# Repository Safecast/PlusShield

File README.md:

PlusShield
==========

The arduino shield for the bGeigie+. Version 1.0.
By Robin Scheibler and Joe Moross.

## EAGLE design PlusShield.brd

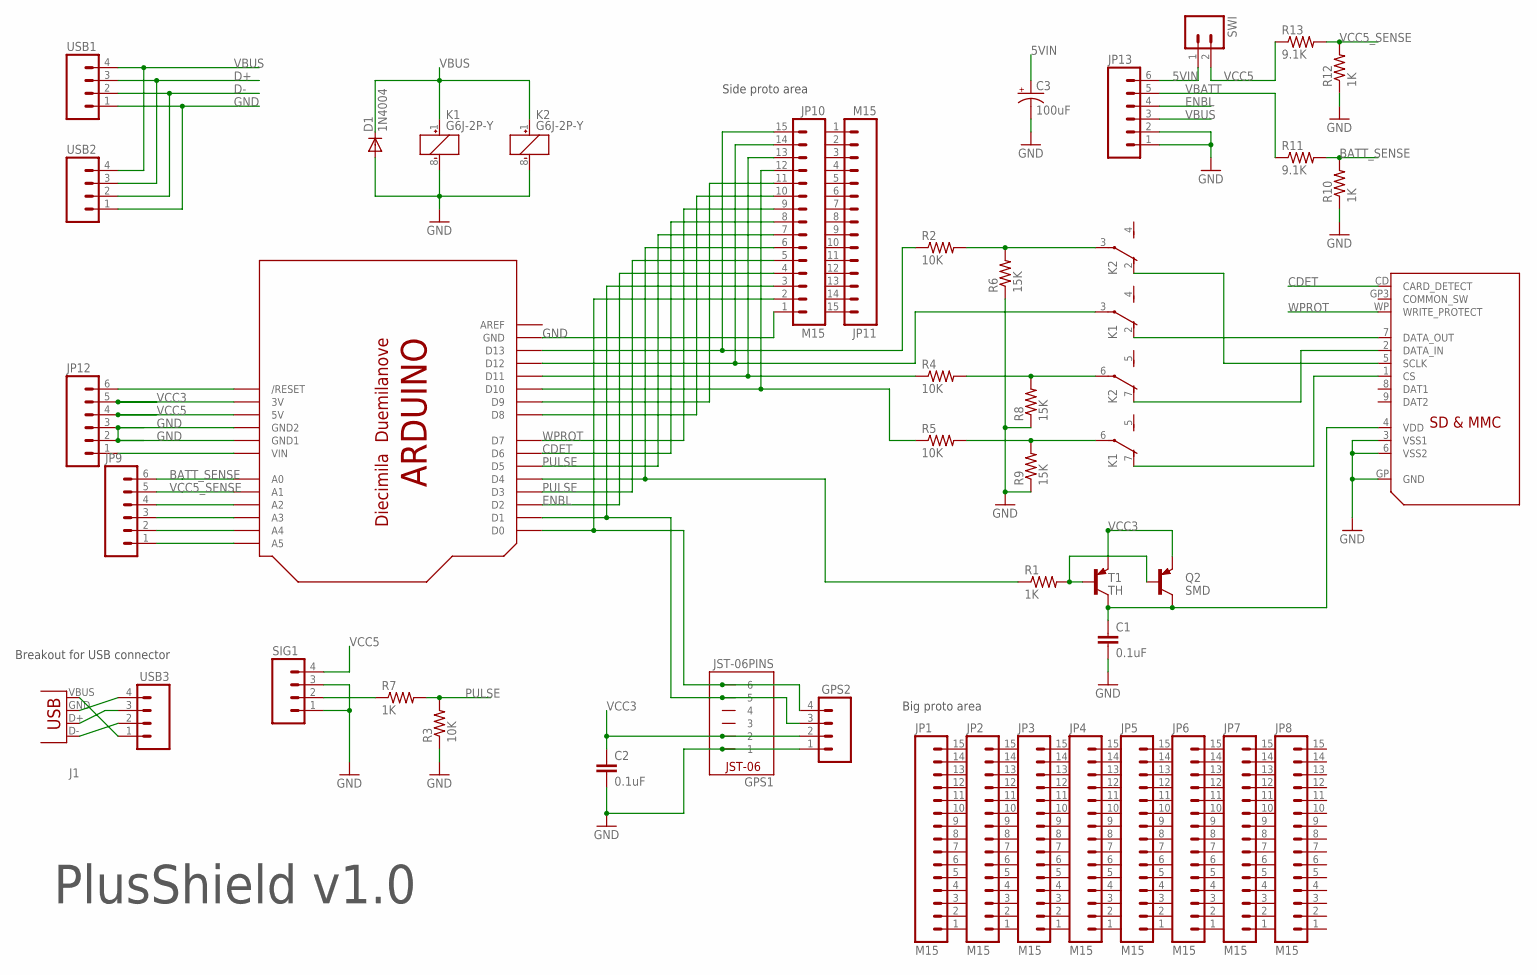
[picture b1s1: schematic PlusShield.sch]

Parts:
C1, C2: 0.1uF; CAP-PTH-5MM
C3: 100uF; EIA7343
D1: 1N4004; DO41-10
GPS1: JST-06PINS; JST-SM06B-SRSS-TB
GPS2: M04PTH; 1X04
J1: USB-A-DIP; A-DIP
JP1, JP2, JP3, JP4, JP5, JP6, JP7, JP8, JP10, JP11: M15; 1X15
JP9, JP12, JP13: M06SIP; 1X06
K1, K2: G6J-2P-Y
Q2: SMD; SOT23
R1, R7, R10, R12: 1K; 0207/10
R2, R3, R4, R5: 10K; 0207/10
R6, R8, R9: 15K; 0207/10
R11, R13: 9.1K; 0207/10
SIG1: M04PTH; 1X04
SWI: M02PTH; 1X02
T1: TH; TO92-CBE
U$1: SDMMC06132; 06132
U$2: ARDUINOSHIELD-NOHOLE; ARDUINO-NOHOLE
USB1, USB2, USB3: M04PTH; 1X04

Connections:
5VIN: C3.A (+), JP13.6, SWI.1
BATT_SENSE: JP9.6, R10.2, R11.2, U$2.A0
CDET: JP10.8, U$1.CD (CARD_DETECT), U$2.D6
D+: USB1.3, USB2.3
D+_C: J1.D+ (D-), USB3.3
D-: USB1.2, USB2.2
D-_C: J1.D- (D+), USB3.2
ENBL: JP10.4, JP13.4, U$2.D2
GND: C1.2, C2.2, C3.C (-), D1.A, GPS1.1, GPS2.1, JP10.1, JP12.2, JP12.3, JP13.1, JP13.2, K1.8 (-), K2.8 (-), R3.1, R6.1, R8.1, R9.1, R10.1, R12.1, SIG1.1, SIG1.3, U$1.3 (VSS1), U$1.6 (VSS2), U$1.GP (GND), U$2.GND, U$2.GND1, U$2.GND2, USB1.1, USB2.1
GND_C: J1.GND (VBUS), USB3.4
unnamed: JP10.6, R1.1, U$2.D4
unnamed: Q2.1 (B), R1.2, T1.B
unnamed: JP10.15, R2.1, U$2.D13
unnamed: JP10.11, U$2.D9
unnamed: JP10.13, R4.1, U$2.D11
unnamed: JP10.12, R5.1, U$2.D10
unnamed: K2.2 (O), U$1.5 (SCLK)
unnamed: K2.3, R2.2, R6.2
unnamed: K2.7 (O), U$1.2 (DATA_IN)
unnamed: K1.7 (O), U$1.1 (CS)
unnamed: K1.2 (O), U$1.7 (DATA_OUT)
unnamed: JP10.14, K1.3, U$2.D12
unnamed: K2.6, R4.2, R8.2
unnamed: K1.6, R5.2, R9.2
unnamed: R7.1, SIG1.2
unnamed: JP10.10, U$2.D8
unnamed: JP12.1, U$2.VIN
unnamed: JP12.6, U$2.RESET (/RESET)
unnamed: JP9.1, U$2.A5
unnamed: JP9.2, U$2.A4
unnamed: JP9.3, U$2.A3
unnamed: JP9.4, U$2.A2
PULSE: JP10.5, JP10.7, R3.2, R7.2, U$2.D3, U$2.D5
RX: GPS1.6, GPS2.4, JP10.2, U$2.D0
TX: GPS1.5, GPS2.3, JP10.3, U$2.D1
VBATT: JP13.5, R11.1
VBUS: D1.C, JP13.3, K1.1 (+), K2.1 (+), USB1.4, USB2.4
VBUS_C: J1.VBUS (GND), USB3.1
VCC3: C2.1, GPS1.2, GPS2.2, JP12.5, Q2.2 (E), T1.E, U$2.3V
VCC5: JP12.4, R13.1, SIG1.4, SWI.2, U$2.5V
VCC5_SENSE: JP9.5, R12.2, R13.2, U$2.A1
VDD: C1.1, Q2.3 (C), T1.C, U$1.4 (VDD)
WPROT: JP10.9, U$1.WP (WRITE_PROTECT), U$2.D7

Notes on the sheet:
Side proto area
Big proto area
Breakout for USB connector
PlusShield v1.0

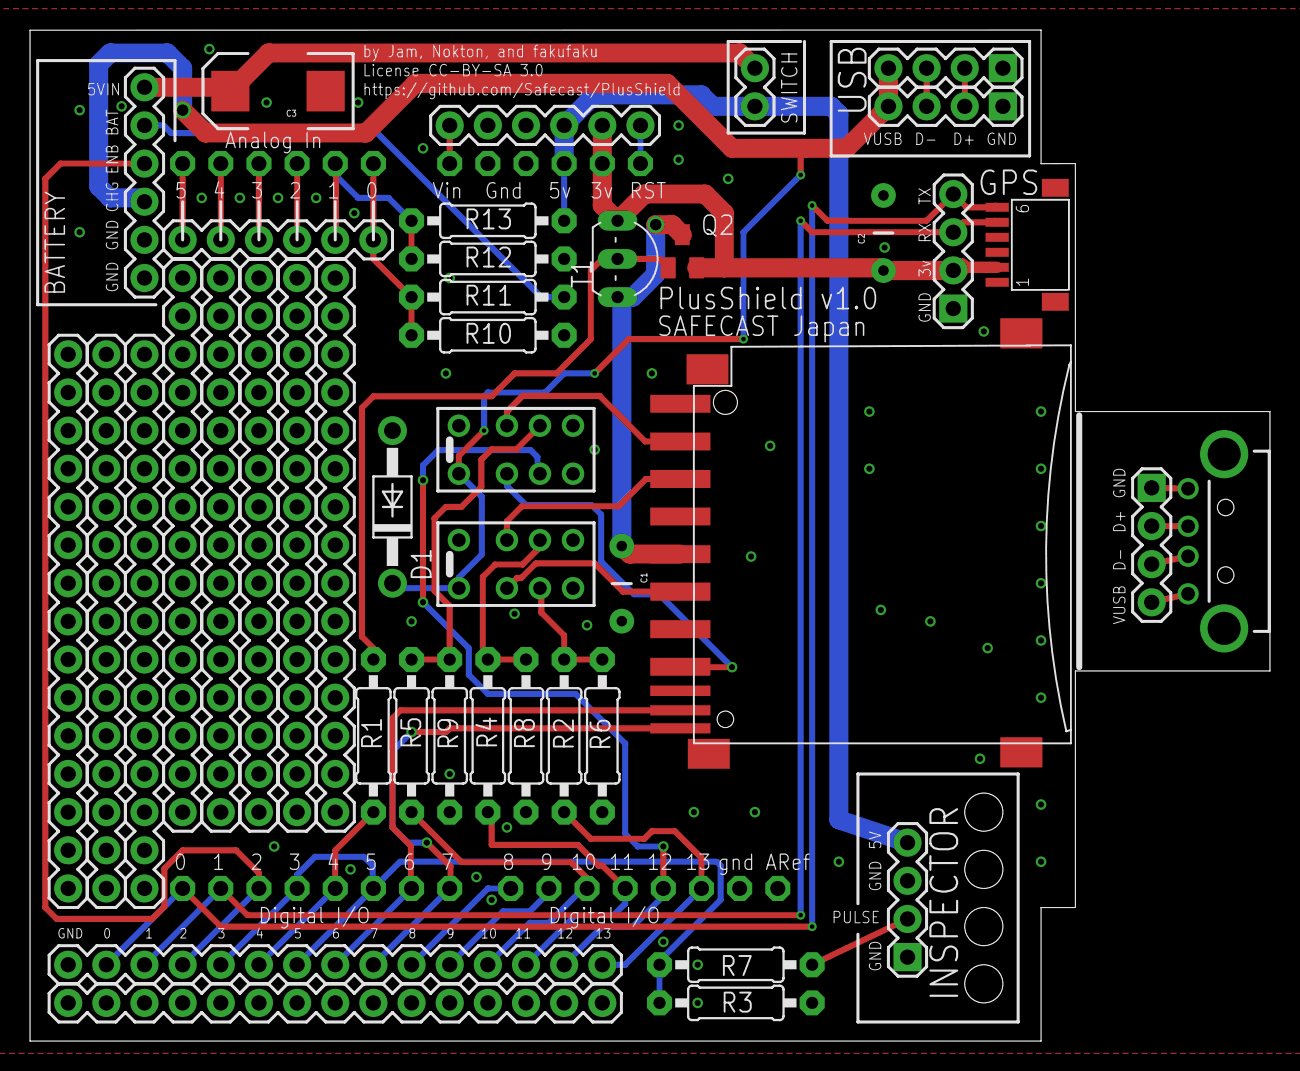
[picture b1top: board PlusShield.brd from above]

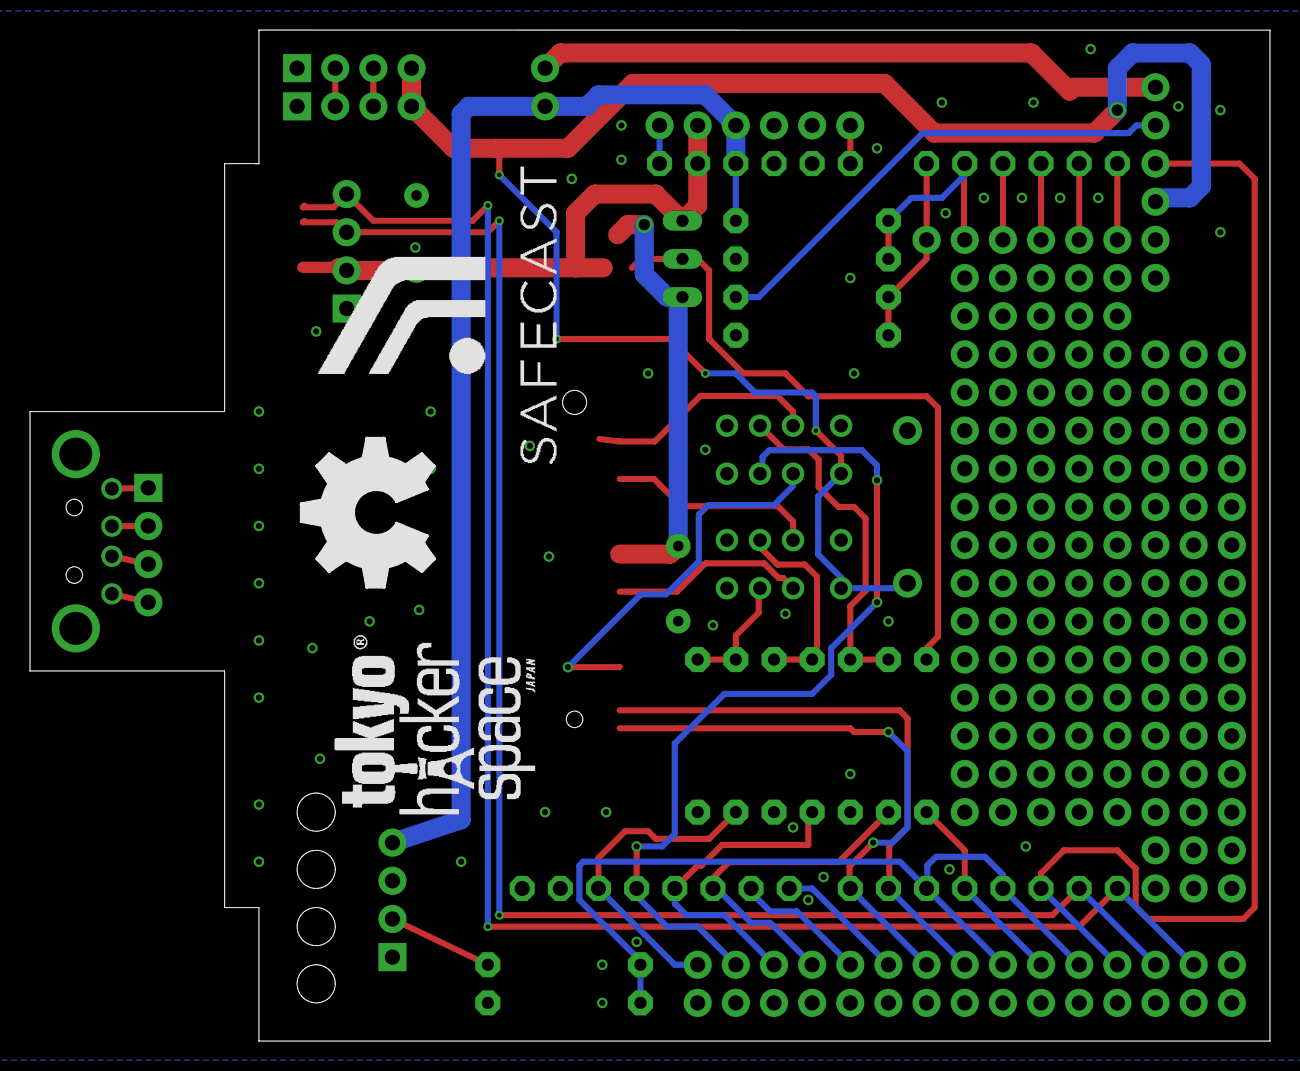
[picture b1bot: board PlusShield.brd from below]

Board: 2 copper layers, 82.5 x 67.3 mm, 47 parts (3 on the bottom side), 43 nets.

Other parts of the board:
U$4: SAFECAST_LOGO
U$6: THS
U$7: OSHW_FILLX350_NOTEXT

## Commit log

2012-07-28 Added schematics and board file.
2012-07-28 Added PNGs and gnd vias.
2012-07-29 Added bigger proto area. Extra holes for arduino pins.
2012-07-29 Small modif to README
2012-07-29 Moved USB connector to other side. Added some labels on silkscreen. Put strain relief holes for Inspector connection. Moved board boundary. Added breakout USB connector dongle.
2012-07-31 Added switch pins. Moved stuff around. Extra connector for GPS.
2012-07-31 Added Gerber.
2012-07-31 Modified credits on board to 'hacker' credits.

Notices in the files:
PlusShield.brd:
License CC-BY-SA 3.0
